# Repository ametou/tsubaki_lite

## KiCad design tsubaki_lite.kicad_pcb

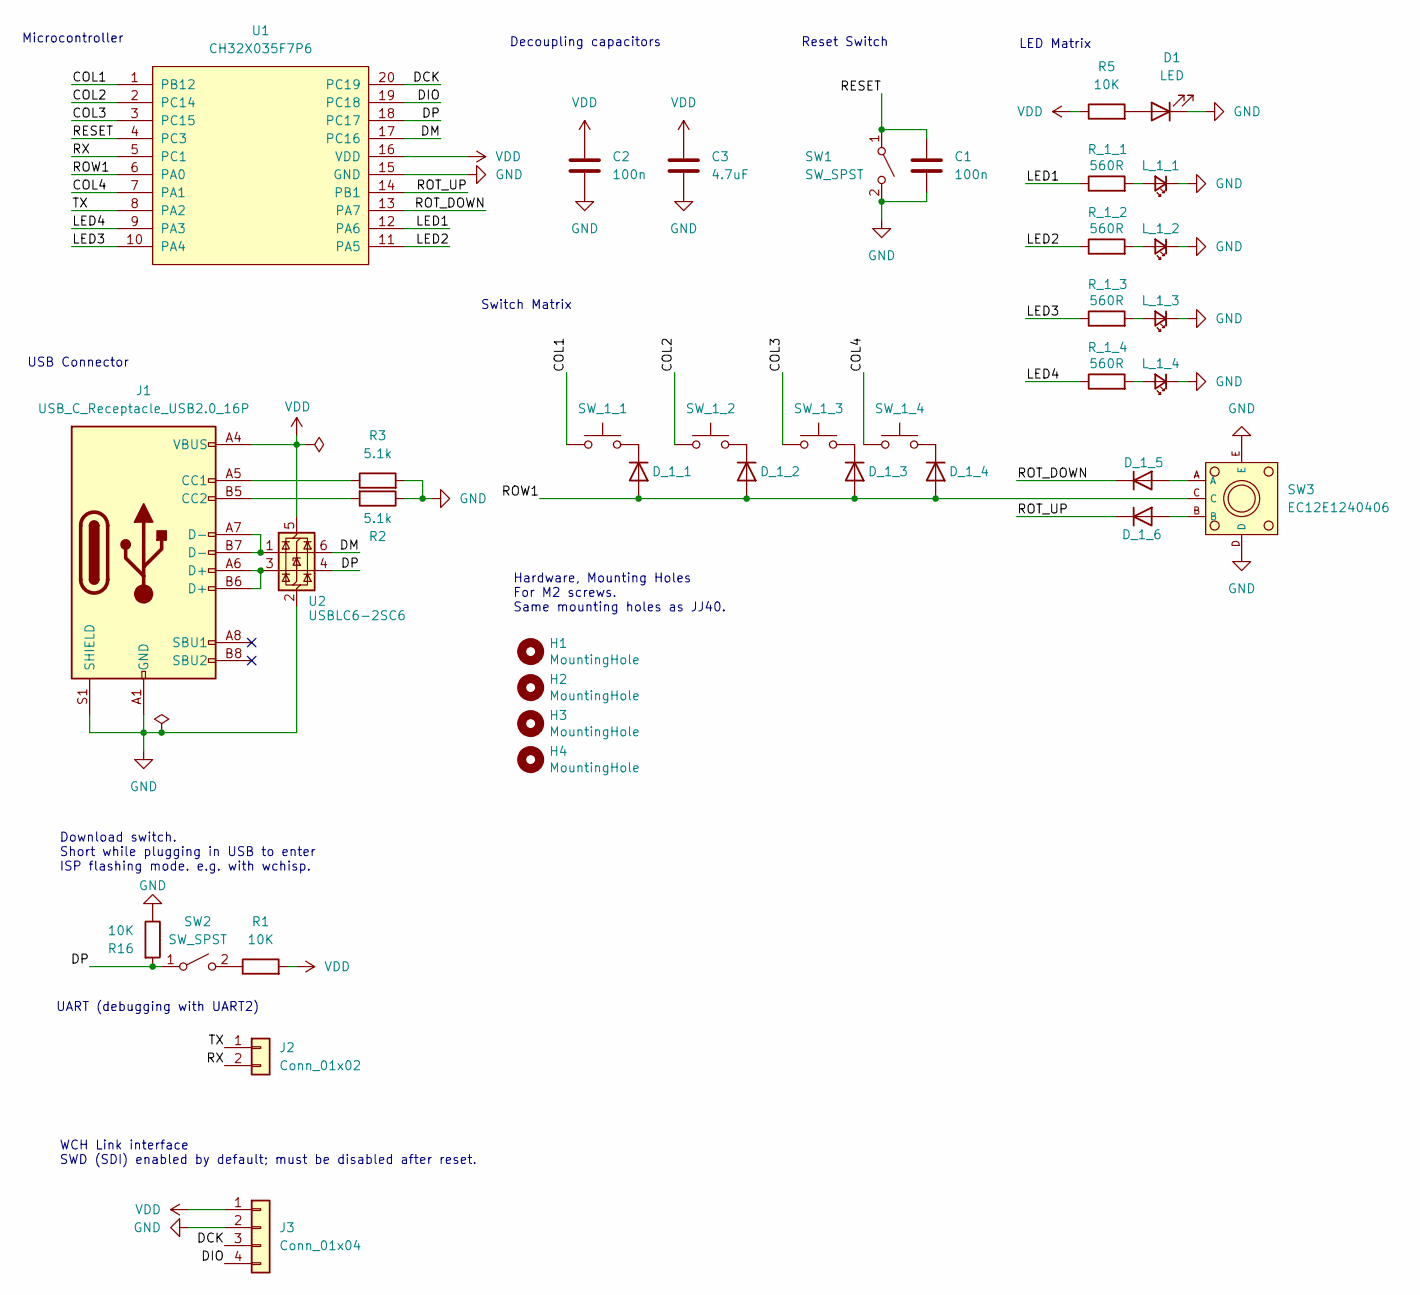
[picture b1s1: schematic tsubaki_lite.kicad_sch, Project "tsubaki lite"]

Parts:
C1, C2: 100n; C_0805_2012Metric; LCSC C49678
C3: 4.7uF; C_0805_2012Metric; LCSC C49678
D1: LED; LED_1206_3216Metric
D_1_1, D_1_2, D_1_3, D_1_4, D_1_5, D_1_6: 1N4148; D_SOD-123; LCSC C9808
H1, H2, H3, H4: MountingHole; MountingHole_2.2mm_M2_DIN965
J1: USB_C_Receptacle_USB2.0_16P; USB_C_Receptacle_HRO_TYPE-C-31-M-12
J2: Conn_01x02; PinHeader_1x02_P2.54mm_Vertical
J3: Conn_01x04; PinHeader_1x04_P2.54mm_Vertical
L_1_1, L_1_2, L_1_3, L_1_4: LED_Small; LED_0805_2012Metric
R1, R5, R16: 10K; R_0805_2012Metric; LCSC C17414
R2, R3: 5.1k; R_0805_2012Metric; LCSC C27834
R_1_1, R_1_2, R_1_3, R_1_4: 560R; R_0402_1005Metric
SW1, SW2: SW_SPST; SW_SPST_B3U-1000P
SW3: EC12E1240406; SW-TH_EC12E1240406; LCSC C351234
SW_1_1, SW_1_2, SW_1_3, SW_1_4: MX-compatible; SW_Cherry_MX_1.00u_PCB
U1: CH32X035F7P6; TSSOP-20_4.4x6.5mm_P0.65mm
U2: USBLC6-2SC6; SOT-23-6

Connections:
/COL1: SW_1_1.1, U1.1 (PB12)
/COL2: SW_1_2.1, U1.2 (PC14)
/COL3: SW_1_3.1, U1.3 (PC15)
/COL4: SW_1_4.1, U1.7 (PA1)
/DCK: J3.3, U1.20 (PC19)
/DIO: J3.4, U1.19 (PC18)
/DM: U1.17 (PC16), U2.6 (I/O1)
/DP: R16.2, SW2.1 (A), U1.18 (PC17), U2.4 (I/O2)
/LED1: R_1_1.1, U1.12 (PA6)
/LED2: R_1_2.1, U1.11 (PA5)
/LED3: R_1_3.1, U1.10 (PA4)
/LED4: R_1_4.1, U1.9 (PA3)
/RESET: C1.1, SW1.1 (A), U1.4 (PC3)
/ROT_DOWN: D_1_5.1 (K), U1.13 (PA7)
/ROT_UP: D_1_6.1 (K), U1.14 (PB1)
/ROW1: D_1_1.2 (A), D_1_2.2 (A), D_1_3.2 (A), D_1_4.2 (A), SW3.C, U1.6 (PA0)
/RX: J2.2, U1.5 (PC1)
/TX: J2.1, U1.8 (PA2)
GND: C1.2, C2.2, C3.2, D1.1 (K), J1.A1 (GND), J1.A12 (GND), J1.B1 (GND), J1.B12 (GND), J1.S1 (SHIELD), J3.2, L_1_1.1 (K), L_1_2.1 (K), L_1_3.1 (K), L_1_4.1 (K), R2.1, R3.2, R16.1, SW1.2 (B), SW3.D, SW3.E, U1.15 (GND), U2.2 (GND)
unnamed: D1.2 (A), R5.2
unnamed: D_1_1.1 (K), SW_1_1.2
unnamed: D_1_2.1 (K), SW_1_2.2
unnamed: D_1_3.1 (K), SW_1_3.2
unnamed: D_1_4.1 (K), SW_1_4.2
unnamed: D_1_5.2 (A), SW3.A
unnamed: D_1_6.2 (A), SW3.B
unnamed: J1.A5 (CC1), R3.1
unnamed: J1.B5 (CC2), R2.2
unnamed: J1.A6 (D+), J1.B6 (D+), U2.3 (I/O2)
unnamed: J1.A7 (D-), J1.B7 (D-), U2.1 (I/O1)
unnamed: L_1_1.2 (A), R_1_1.2
unnamed: L_1_2.2 (A), R_1_2.2
unnamed: L_1_3.2 (A), R_1_3.2
unnamed: L_1_4.2 (A), R_1_4.2
unnamed: R1.1, SW2.2 (B)
VDD: C2.1, C3.1, J1.A4 (VBUS), J1.A9 (VBUS), J1.B4 (VBUS), J1.B9 (VBUS), J3.1, R1.2, R5.1, U1.16 (VDD), U2.5 (VBUS)

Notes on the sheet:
Microcontroller
USB Connector
WCH Link interface SWD (SDI) enabled by default; must be disabled after reset.
Download switch. Short while plugging in USB to enter ISP flashing mode. e.g. with wchisp.
Decoupling capacitors
Switch Matrix
UART (debugging with UART2)
Reset Switch
Hardware, Mounting Holes For M2 screws. Same mounting holes as JJ40.
LED Matrix

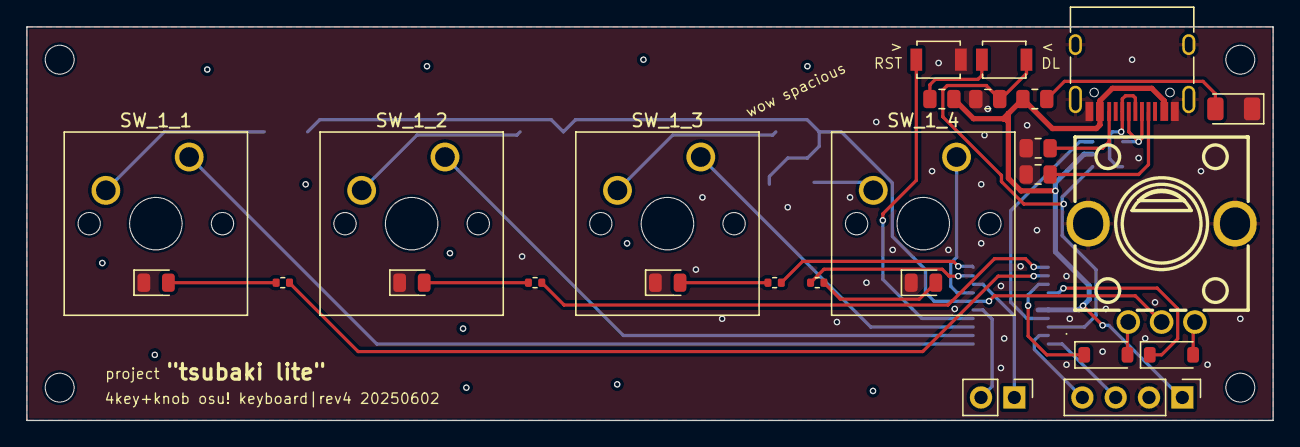
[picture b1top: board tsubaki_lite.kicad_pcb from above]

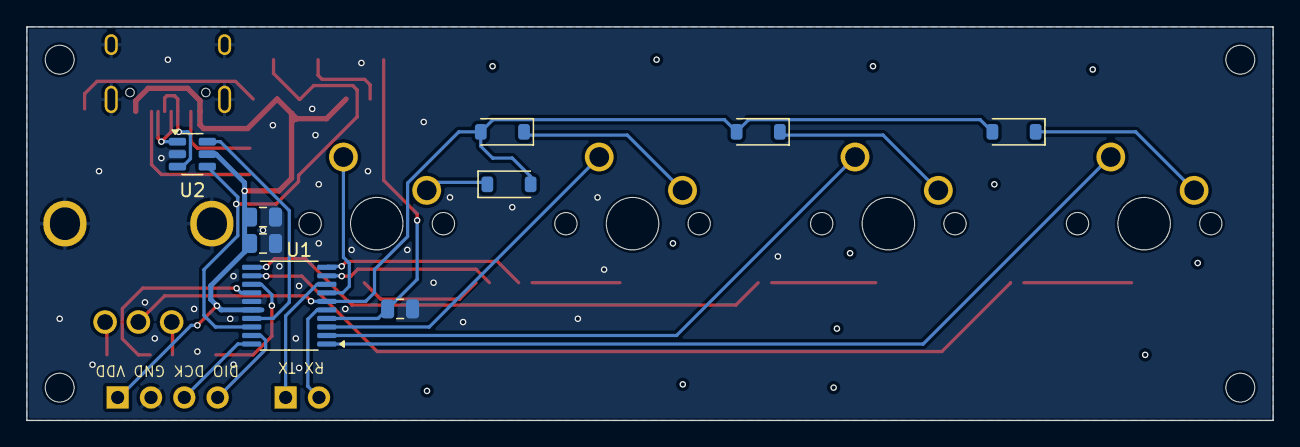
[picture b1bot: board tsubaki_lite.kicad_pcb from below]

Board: 2 copper layers, 95.0 x 30.0 mm, 39 parts (9 on the bottom side), 36 nets.

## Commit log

2025-05-22 rev2
2025-05-23 Create LICENSE
2025-05-27 rev3
2025-06-12 rev4
